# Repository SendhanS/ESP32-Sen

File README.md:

# ESP32-Sen
A compact ESP32-S3-MINI-1-N8 development board with USB-C (ESD protected), a 4-layer PCB stack-up (signal / GND / power / signal), and 3.3 V regulation using the TLV75801. Includes GPIO buttons, a WS2812B status LED, and space for an onboard I²C OLED breakout.
The board is intended for learning, experimentation, and portfolio demonstration of embedded systems and PCB design practices.
Status: Not yet tested.
The design is functional in theory but may require revisions and improvements after bring-up.

**Overview**

This board provides a clean ESP32-S3 core with USB-C connectivity, proper ESD protection, a structured 4-layer PCB stack-up, and expansion options for basic UI and peripherals. The goal was to move beyond simple 2-layer hobby boards and design something closer to real-world embedded hardware.

**Key Features**

ESP32-S3-MINI-1-N8 module

USB-C connector (USB4105)

Differential USB D+ / D− routing

ESD protection using D3V3XA4B10LP TVS diodes

TLV75801 linear regulator (5 V USB → 3.3 V)

4-layer PCB stack-up:

Top: Signal + components

Inner 1: Solid GND plane

Inner 2: Power plane (3.3 V)

Bottom: Signal routing

WS2812B RGB status LED

BOOT and RESET buttons

Two additional GPIO buttons (GPIO4, GPIO5)

**Power Architecture**

Primary power input via USB-C (5 V)

Onboard TLV75801 LDO generates 3.3 V for ESP32 and peripherals

3.3 V rail is exposed on headers for external devices

Design allows future extension for alternative power input with minor modifications

I²C header and reserved space for a 0.91" OLED display module

GPIO headers for expansion

**USB Design Notes**

USB D+ and D− routed as a differential pair

Length-matched and impedance-aware routing

ESD protection placed close to the USB connector

Intended for USB device mode (programming and serial communication)

**I²C and Display Support**

Dedicated I²C header (3.3 V logic)

PCB space reserved for a common 0.91" 128×32 I²C OLED module

Display is optional and not populated by default

**Known Limitations / Future Improvements**

Board has not been fabricated or tested yet

No battery power or charging circuit

No current measurement or power monitoring

Firmware bring-up examples not included yet

OLED mounting footprint may need adjustment depending on module vendor

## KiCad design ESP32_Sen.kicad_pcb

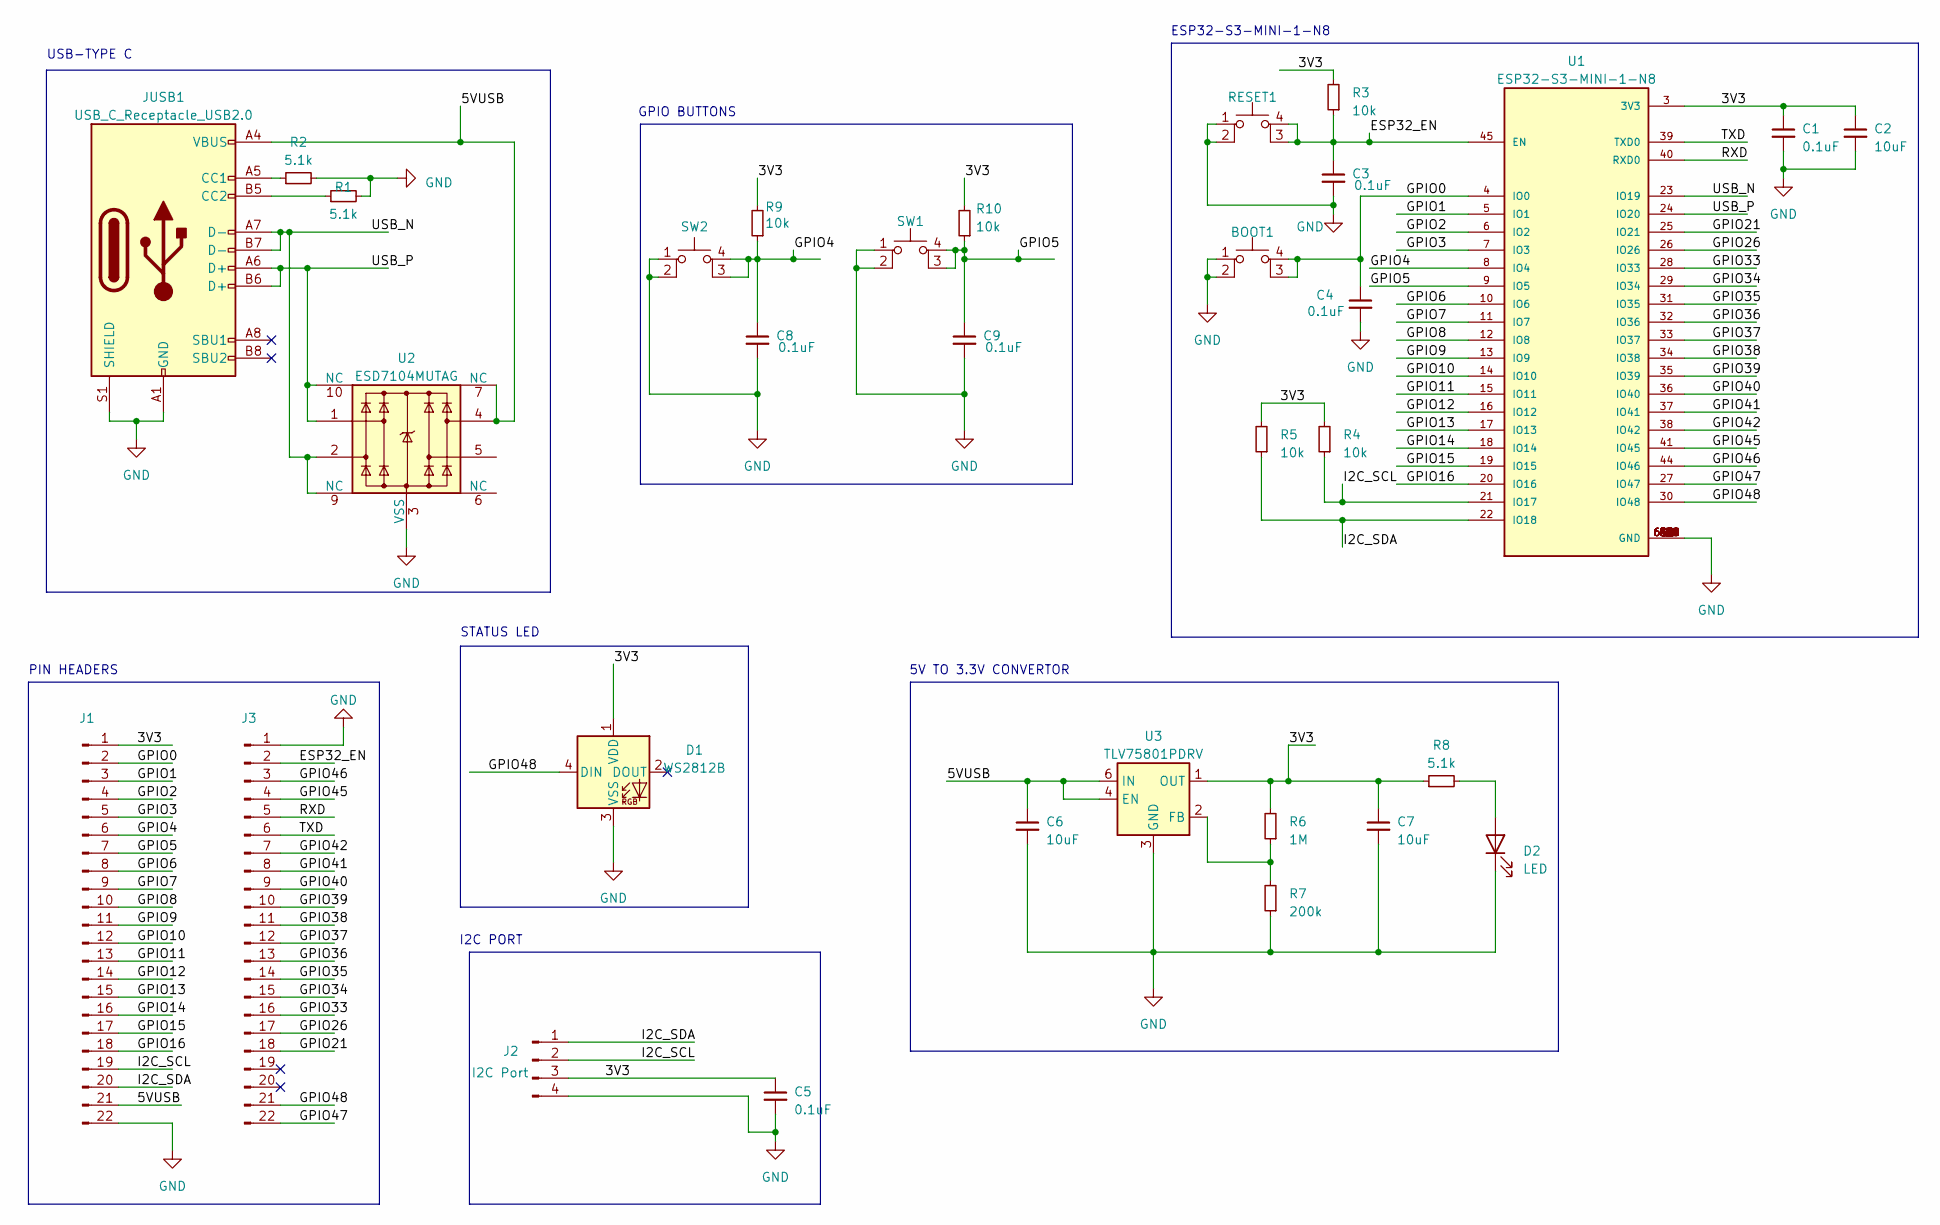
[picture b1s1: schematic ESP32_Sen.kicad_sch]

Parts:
BOOT1: SW_SPST_PTS810
C1, C3, C4, C5, C8, C9: 0.1uF; C_0603_1608Metric
C2, C6, C7: 10uF; C_0603_1608Metric
D1: WS2812B; LED_WS2812B_PLCC4_5.0x5.0mm_P3.2mm
D2: LED; LED_0603_1608Metric
J1, J3: PinHeader_1x22_P2.54mm_Vertical
J2: I2C Port; PinSocket_1x04_P2.54mm_Vertical
JUSB1: USB_C_Receptacle_USB2.0; USB_C_Receptacle_GCT_USB4105-xx-A_16P_TopMnt_Horizontal
R1, R2, R8: 5.1k; R_0603_1608Metric
R3, R4, R5, R9, R10: 10k; R_0603_1608Metric
R6: 1M; R_0603_1608Metric
R7: 200k; R_0603_1608Metric
RESET1: SW_SPST_PTS810
SW1, SW2: SW_MEC_5E; SW_SPST_PTS810
U1: ESP32-S3-MINI-1-N8; XCVR_ESP32-S3-MINI-1-N8; PARTREV v0.6
U2: ESD7104MUTAG; Diodes_UDFN-10_1.0x2.5mm_P0.5mm
U3: TLV75801PDRV; WSON-6-1EP_2x2mm_P0.65mm_EP1x1.6mm

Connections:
/3V3: C1.1, C2.1, C5.1, C7.1, D1.1 (VDD), J1.1, J2.3, R3.2, R4.2, R5.2, R6.2, R8.1, R9.2, R10.2, U1.3 (3V3), U3.1 (OUT)
/5VUSB: C6.1, J1.21, JUSB1.A4 (VBUS), JUSB1.A9 (VBUS), JUSB1.B4 (VBUS), JUSB1.B9 (VBUS), U2.4, U2.7 (NC), U3.4 (EN), U3.6 (IN)
/ESP32_EN: C3.1, J3.2, R3.1, RESET1.3 (K), RESET1.4 (A), U1.45 (EN)
/GPIO0: BOOT1.3 (K), BOOT1.4 (A), C4.1, J1.2, U1.4 (IO0)
/GPIO1: J1.3, U1.5 (IO1)
/GPIO2: J1.4, U1.6 (IO2)
/GPIO3: J1.5, U1.7 (IO3)
/GPIO4: C8.1, J1.6, R9.1, SW2.3 (K), SW2.4 (A), U1.8 (IO4)
/GPIO5: C9.1, J1.7, R10.1, SW1.3 (K), SW1.4 (A), U1.9 (IO5)
/GPIO6: J1.8, U1.10 (IO6)
/GPIO7: J1.9, U1.11 (IO7)
/GPIO8: J1.10, U1.12 (IO8)
/GPIO9: J1.11, U1.13 (IO9)
/GPIO10: J1.12, U1.14 (IO10)
/GPIO11: J1.13, U1.15 (IO11)
/GPIO12: J1.14, U1.16 (IO12)
/GPIO13: J1.15, U1.17 (IO13)
/GPIO14: J1.16, U1.18 (IO14)
/GPIO15: J1.17, U1.19 (IO15)
/GPIO16: J1.18, U1.20 (IO16)
/GPIO21: J3.18, U1.25 (IO21)
/GPIO26: J3.17, U1.26 (IO26)
/GPIO33: J3.16, U1.28 (IO33)
/GPIO34: J3.15, U1.29 (IO34)
/GPIO35: J3.14, U1.31 (IO35)
/GPIO36: J3.13, U1.32 (IO36)
/GPIO37: J3.12, U1.33 (IO37)
/GPIO38: J3.11, U1.34 (IO38)
/GPIO39: J3.10, U1.35 (IO39)
/GPIO40: J3.9, U1.36 (IO40)
/GPIO41: J3.8, U1.37 (IO41)
/GPIO42: J3.7, U1.38 (IO42)
/GPIO45: J3.4, U1.41 (IO45)
/GPIO46: J3.3, U1.44 (IO46)
/GPIO47: J3.22, U1.27 (IO47)
/GPIO48: D1.4 (DIN), J3.21, U1.30 (IO48)
/I2C_SCL: J1.19, J2.2, R4.1, U1.21 (IO17)
/I2C_SDA: J1.20, J2.1, R5.1, U1.22 (IO18)
/RXD: J3.5, U1.40 (RXD0)
/TXD: J3.6, U1.39 (TXD0)
/USB_N: JUSB1.A7 (D-), JUSB1.B7 (D-), U1.23 (IO19), U2.2, U2.9 (NC)
/USB_P: JUSB1.A6 (D+), JUSB1.B6 (D+), U1.24 (IO20), U2.1, U2.10 (NC)
GND: BOOT1.1, BOOT1.2, C1.2, C2.2, C3.2, C4.2, C5.2, C6.2, C7.2, C8.2, C9.2, D1.3 (VSS), D2.1 (K), J1.22, J2.4, J3.1, JUSB1.A1 (GND), JUSB1.A12 (GND), JUSB1.B1 (GND), JUSB1.B12 (GND), JUSB1.S1 (SHIELD), R1.2, R2.2, R7.1, RESET1.1, RESET1.2, SW1.1, SW1.2, SW2.1, SW2.2, U1.1 (GND), U1.2 (GND), U1.42 (GND), U1.43 (GND), U1.46 (GND), U1.47 (GND), U1.48 (GND), U1.49 (GND), U1.50 (GND), U1.51 (GND), U1.52 (GND), U1.53 (GND), U1.54 (GND), U1.55 (GND), U1.56 (GND), U1.57 (GND), U1.58 (GND), U1.59 (GND), U1.60 (GND), U1.61 (GND), U1.61_1 (GND), U1.61_2 (GND), U1.61_3 (GND), U1.61_4 (GND), U1.61_5 (GND), U1.61_6 (GND), U1.61_7 (GND), U1.61_8 (GND), U1.62 (GND), U1.63 (GND), U1.64 (GND), U1.65 (GND), U2.3 (VSS), U2.8 (VSS), U3.3 (GND), U3.7 (GND)
unnamed: D2.2 (A), R8.2
unnamed: JUSB1.A5 (CC1), R2.1
unnamed: JUSB1.B5 (CC2), R1.1
unnamed: R6.1, R7.2, U3.2 (FB)

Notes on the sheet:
STATUS LED
ESP32-S3-MINI-1-N8
PIN HEADERS
5V TO 3.3V CONVERTOR
GPIO BUTTONS
USB-TYPE C
I2C PORT

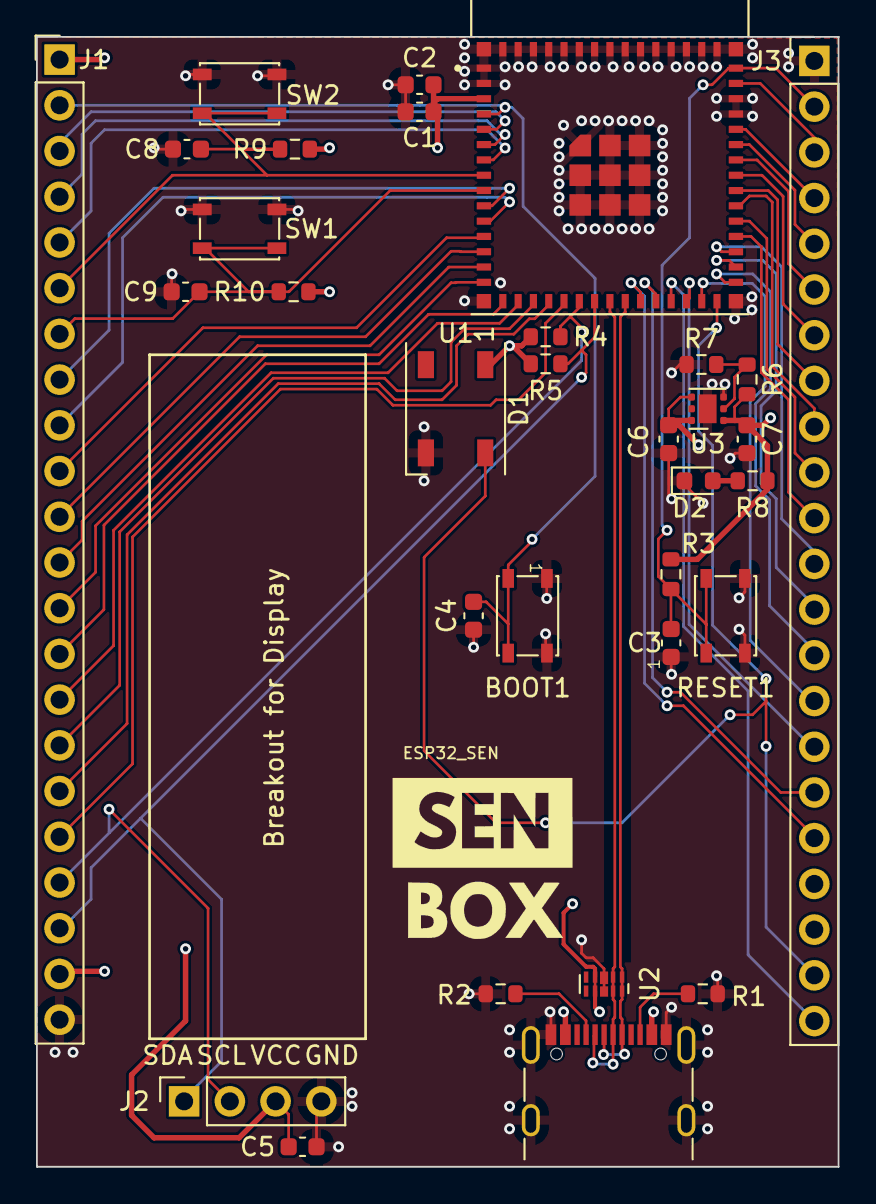
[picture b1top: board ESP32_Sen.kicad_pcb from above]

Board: 4 copper layers, 44.5 x 62.8 mm, 32 parts (0 on the bottom side), 47 nets.
